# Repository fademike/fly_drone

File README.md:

# fly_drone

My example drone. (in development)

How to connect:
Android phone (AppFlyControl) <-> usb-uart(example: cp2102) <-> uart->rf (STM8S003_AND_SI4463) <-> fly_drone
<br>
or:
<br>
Android phone (QGroundControl or AppFlyControl) <-wifi-> Linux PC (flyLinuxServer) <-> uart->rf (STM8S003_AND_SI4463) <-> fly_drone

on board:
- DC-DC for 2,3,..S battery operation. To operate on a 1S battery, it is necessary to replace the components to turn off the DC-DC.
- RF SI4463 433MHz radio transceiver. when changing the frequency, you can to change components and programmatically set a different frequency.
- imu mpu6050
- 4pcs 3-pin connector for servo motor/ESC (IMP 1-2 ms) for 4pcs brushed motors need to set mosfet or esc for brushed motors.
- i2c connector, for example: for VL53L0X
- connector for debugging by swdio/uart

For connect brushed motors with esc or servo motor, you can use convertor on attiny13a. example: kicad->tiny_2nmosfet.
For connect 4pcs brushed motors, you can use n-mosfet on every channel.

<br>
Code:
<br>
bootloader (update firmware via RF by FlyLinuxServer)<br>
fly_drone<br>
- mavlink protocol:<br>
-- params list settings(PID, mux chan, motor settings, orientation)<br>
-- RC_CHANNELS<br>
-- COMMAND_LONG - ARM_DISARM/CALIBRATION/REBOOT<br>
-- MSG_STATUSTEXT - logs<br>
- imu, rf, vl53l0x<br>
- acc and gyro calibrate<br>
- for save params and acc calibrate on flash, need to change "flash_params"<br>
- it is compatible with qgroungcontrol (tested on android)<br>
<br>
And in repository:<br>
kicad:<br>
- ESC_atmega8 - esc for brashless motor. (need to changed frequency by fuses)<br>
- stm32f103_Fly.. - fly_drone project<br>
- tiny_2nmosfet - esc for connection 4 brashed motors(independent 4 in, 4 out)<br>
<br>
video fly_drone.mpg in video repository

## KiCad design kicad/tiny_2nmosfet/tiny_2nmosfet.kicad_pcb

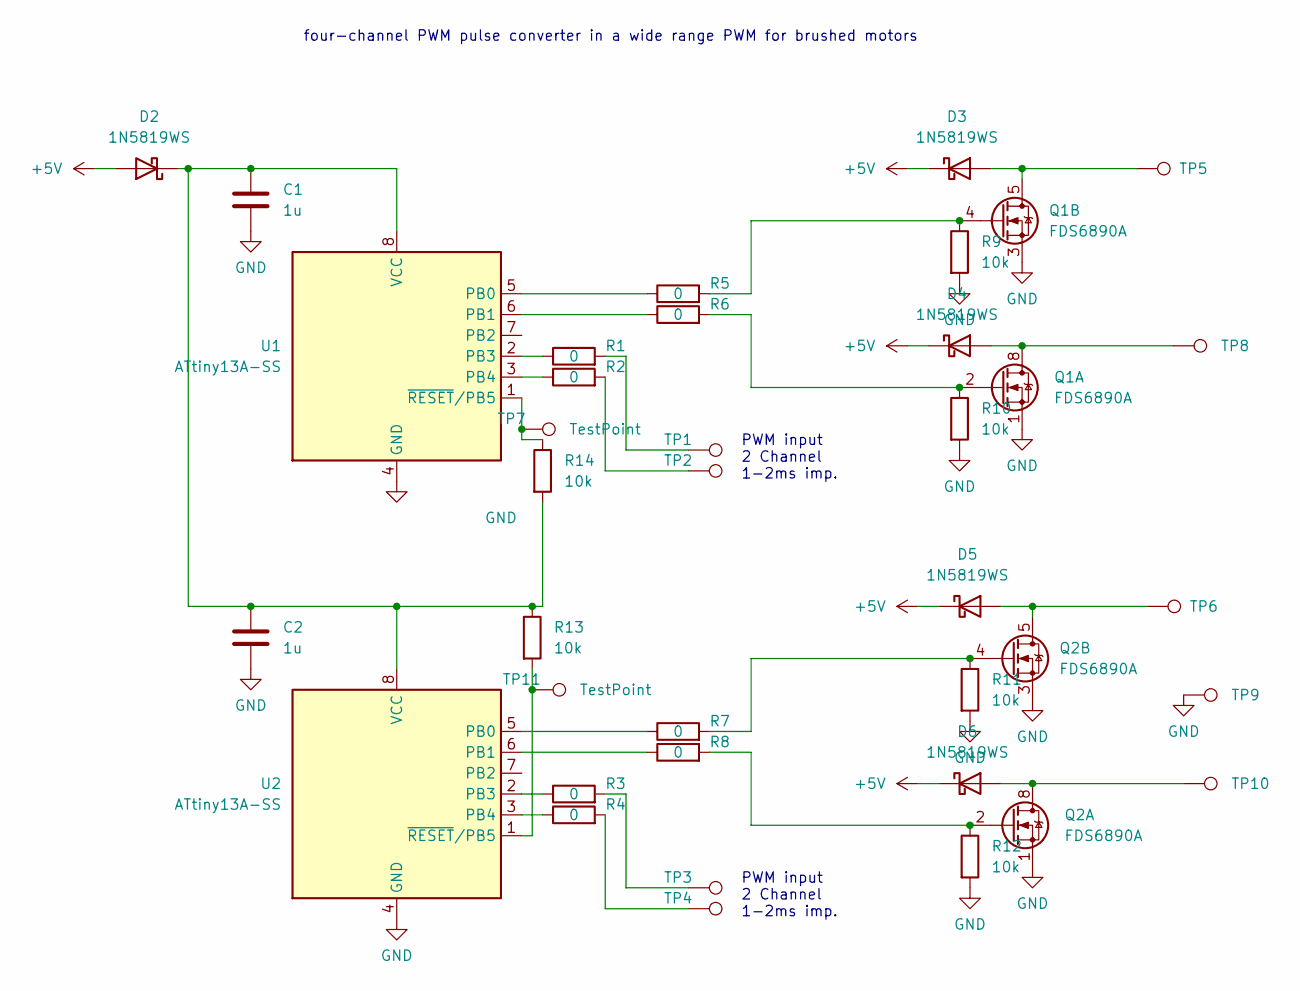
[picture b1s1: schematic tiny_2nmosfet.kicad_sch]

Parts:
C1, C2: 1u; C_0603_1608Metric
D2, D3, D4, D5, D6: 1N5819WS; D_SOD-323
Q1, Q2: FDS6890A; SOIC-8_3.9x4.9mm_P1.27mm
R1, R2, R3, R4, R5, R6, R7, R8: 0; R_0603_1608Metric
R9, R10, R11, R12, R13, R14: 10k; R_0603_1608Metric
TP1, TP2, TP3, TP4, TP5, TP6, TP7, TP8, TP9, TP10, TP11: TestPoint; PinHeader_1x01_P2.54mm_Vertical
U1, U2: ATtiny13A-SS; SOIC-8_3.9x4.9mm_P1.27mm

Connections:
+5V: D2.2 (A), D3.1 (K), D4.1 (K), D5.1 (K), D6.1 (K)
GND: C1.2, C2.2, Q1.1 (S1), Q1.3 (S2), Q2.1 (S1), Q2.3 (S2), R9.2, R10.2, R11.2, R12.2, TP9.1, U1.4 (GND), U2.4 (GND)
unnamed: C1.1, C2.1, D2.1 (K), R13.1, R14.2, U1.8 (VCC), U2.8 (VCC)
unnamed: D3.2 (A), Q1.5 (D2), Q1.6 (D2), TP5.1
unnamed: D4.2 (A), Q1.7 (D1), Q1.8 (D1), TP8.1
unnamed: D5.2 (A), Q2.5 (D2), Q2.6 (D2), TP6.1
unnamed: D6.2 (A), Q2.7 (D1), Q2.8 (D1), TP10.1
unnamed: Q1.2 (G1), R6.2, R10.1
unnamed: Q1.4 (G2), R5.2, R9.1
unnamed: Q2.2 (G1), R8.2, R12.1
unnamed: Q2.4 (G2), R7.2, R11.1
unnamed: R1.2, TP1.1
unnamed: R2.2, TP2.1
unnamed: R3.2, TP3.1
unnamed: R4.2, TP4.1
unnamed: R5.1, U1.5 (PB0)
unnamed: R6.1, U1.6 (PB1)
unnamed: R1.1, U1.2 (PB3)
unnamed: R2.1, U1.3 (PB4)
unnamed: R14.1, TP7.1, U1.1 (~RESET/PB5)
unnamed: R7.1, U2.5 (PB0)
unnamed: R8.1, U2.6 (PB1)
unnamed: R3.1, U2.2 (PB3)
unnamed: R4.1, U2.3 (PB4)
unnamed: R13.2, TP11.1, U2.1 (~RESET/PB5)

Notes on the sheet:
PWM input 2 Channel 1-2ms imp.
four-channel PWM pulse converter in a wide range PWM for brushed motors

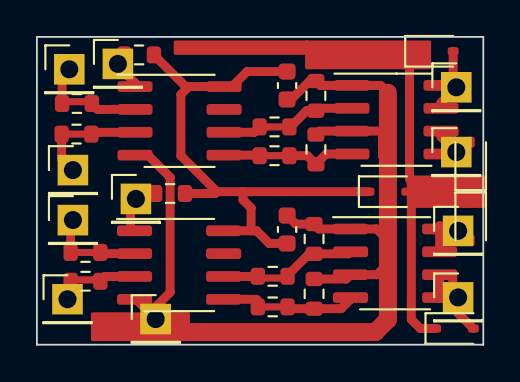
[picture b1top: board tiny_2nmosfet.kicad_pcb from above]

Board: 2 copper layers, 24.8 x 17.1 mm, 36 parts (0 on the bottom side), 25 nets.

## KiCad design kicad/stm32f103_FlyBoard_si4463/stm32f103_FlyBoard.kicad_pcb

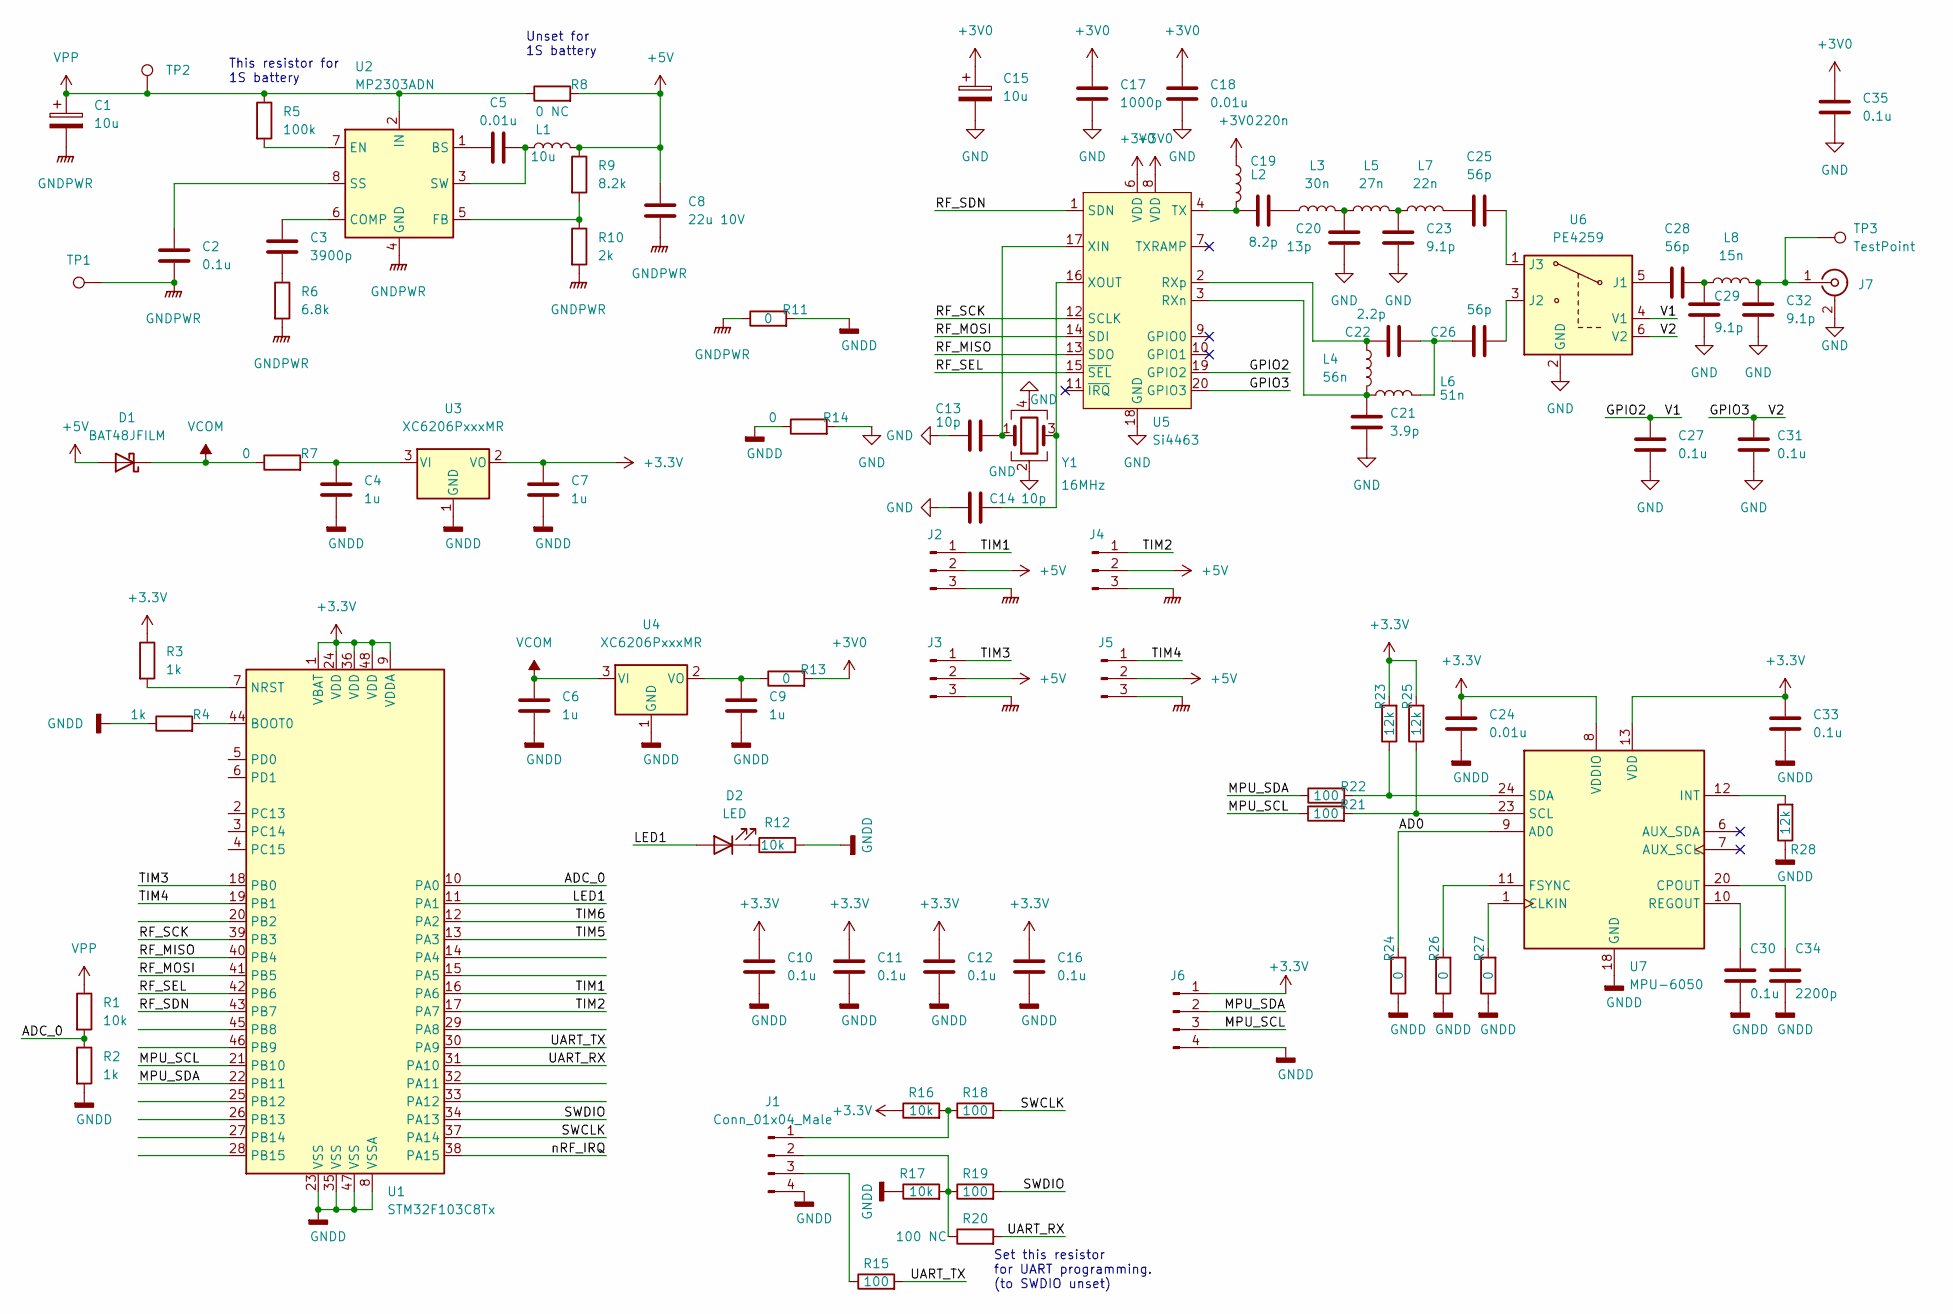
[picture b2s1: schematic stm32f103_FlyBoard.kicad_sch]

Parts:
C1: 10u; CP_EIA-3528-21_Kemet-B
C2, C10, C11, C12, C16, C27, C30, C31, C33, C35: 0.1u; C_0402_1005Metric
C3: 3900p; C_0402_1005Metric
C4, C6, C7, C9: 1u; C_0402_1005Metric
C5, C18, C24: 0.01u; C_0402_1005Metric
C8: 22u 10V; C_0805_2012Metric
C13, C14: 10p; C_0402_1005Metric
C15: 10u; CP_EIA-3216-18_Kemet-A
C17: 1000p; C_0402_1005Metric
C19: 8.2p; C_0402_1005Metric
C20: 13p; C_0402_1005Metric
C21: 3.9p; C_0402_1005Metric
C22: 2.2p; C_0402_1005Metric
C23, C29, C32: 9.1p; C_0402_1005Metric
C25, C26, C28: 56p; C_0402_1005Metric
C34: 2200p; C_0402_1005Metric
D1: BAT48JFILM; D_SOD-323
D2: LED; LED_0805_2012Metric
J1, J6: Conn_01x04_Male; Molex_PicoBlade_53047-0410_1x04_P1.25mm_Vertical
J2, J3, J4, J5: Conn_01x03_Male; Molex_PicoBlade_53047-0310_1x03_P1.25mm_Vertical
J7: Conn_Coaxial; U.FL_Hirose_U.FL-R-SMT-1_Vertical
L1: 10u; L_Bourns-SRN6028
L2: 220n; L_0402_1005Metric
L3: 30n; L_0402_1005Metric
L4: 56n; L_0402_1005Metric
L5: 27n; L_0402_1005Metric
L6: 51n; L_0402_1005Metric
L7: 22n; L_0402_1005Metric
L8: 15n; L_0402_1005Metric
R1, R12, R17: 10k; R_0402_1005Metric
R2, R3, R4: 1k; R_0402_1005Metric
R5: 100k; R_0402_1005Metric
R6: 6.8k; R_0402_1005Metric
R7, R11, R13, R14: 0; R_0805_2012Metric
R8: 0 NC; R_0805_2012Metric
R9: 8.2k; R_0402_1005Metric
R10: 2k; R_0402_1005Metric
R15, R18, R19, R21, R22: 100; R_0402_1005Metric
R16: 10k; R_0603_1608Metric
R20: 100 NC; R_0402_1005Metric
R23, R25, R28: 12k; R_0402_1005Metric
R24, R26, R27: 0; R_0402_1005Metric
TP1, TP2, TP3: TestPoint; TestPoint_Pad_D1.0mm
U1: STM32F103C8Tx; LQFP-48_7x7mm_P0.5mm
U2: MP2303ADN; SOIC-8-1EP_3.9x4.9mm_P1.27mm_EP2.62x3.51mm
U3, U4: XC6206PxxxMR; SOT-23
U5: Si4463; QFN-20-1EP_4x4mm_P0.5mm_EP2.6x2.6mm
U6: PE4259; SOT-363_SC-70-6
U7: MPU-6050; InvenSense_QFN-24_4x4mm_P0.5mm
Y1: 16MHz; Crystal_SMD_SeikoEpson_FA238-4Pin_3.2x2.5mm

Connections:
+3.3V: C7.1, C10.1, C11.1, C12.1, C16.1, C24.1, C33.1, J6.1, R3.1, R16.1, R23.2, R25.2, U1.1 (VBAT), U1.9 (VDDA), U1.24 (VDD), U1.36 (VDD), U1.48 (VDD), U3.2 (VO), U7.8 (VDDIO), U7.13 (VDD)
+3V0: C15.1, C17.1, C18.1, C35.1, L2.1, R13.2, U5.6 (VDD), U5.8 (VDD)
+5V: C8.1, D1.2 (A), J2.2, J3.2, J4.2, J5.2, L1.2, R8.2, R9.1
/AD0: R24.2, U7.9 (AD0)
/ADC_0: R1.2, R2.1, U1.10 (PA0)
/GPIO2: C27.2, U5.19 (GPIO2), U6.4 (V1)
/GPIO3: C31.2, U5.20 (GPIO3), U6.6 (V2)
/LED1: D2.2 (A), U1.11 (PA1)
/MPU_SCL: J6.3, R21.1, U1.21 (PB10)
/MPU_SDA: J6.2, R22.1, U1.22 (PB11)
/RF_MISO: U1.40 (PB4), U5.13 (SDO)
/RF_MOSI: U1.41 (PB5), U5.14 (SDI)
/RF_SCK: U1.39 (PB3), U5.12 (SCLK)
/RF_SDN: U1.43 (PB7), U5.1 (SDN)
/RF_SEL: U1.42 (PB6), U5.15 (~SEL)
/SWCLK: R18.2, U1.37 (PA14)
/SWDIO: R19.2, U1.34 (PA13)
/TIM1: J2.1, U1.16 (PA6)
/TIM2: J4.1, U1.17 (PA7)
/TIM3: J3.1, U1.18 (PB0)
/TIM4: J5.1, U1.19 (PB1)
/TIM5: U1.13 (PA3)
/TIM6: U1.12 (PA2)
/UART_RX: R20.2, U1.31 (PA10)
/UART_TX: R15.2, U1.30 (PA9)
/nRF_IRQ: U1.38 (PA15)
GND: C13.1, C14.1, C15.2, C17.2, C18.2, C20.1, C21.1, C23.1, C27.1, C29.1, C31.1, C32.1, C35.2, J7.2 (Ext), R14.2, U5.18 (GND), U5.21 (GND), U6.2 (GND), Y1.2, Y1.4
GNDD: C4.2, C6.2, C7.2, C9.2, C10.2, C11.2, C12.2, C16.2, C24.2, C30.2, C33.2, C34.2, J1.4, J6.4, R2.2, R4.1, R11.2, R12.2, R14.1, R17.1, R24.1, R26.1, R27.1, R28.1, U1.8 (VSSA), U1.23 (VSS), U1.35 (VSS), U1.47 (VSS), U3.1 (GND), U4.1 (GND), U7.18 (GND)
GNDPWR: C1.2, C2.2, C8.2, J2.3, J3.3, J4.3, J5.3, R6.2, R10.2, R11.1, TP1.1, U2.4 (GND)
unnamed: C3.2, R6.1
unnamed: C19.2, L3.1
unnamed: C20.2, L3.2, L5.1
unnamed: C22.2, C26.1, L6.2
unnamed: C23.2, L5.2, L7.1
unnamed: C25.2, L7.2
unnamed: C28.1, C29.2, L8.1
unnamed: D2.1 (K), R12.1
unnamed: J1.1, R16.2, R18.1
unnamed: J1.2, R17.2, R19.1, R20.1
unnamed: J1.3, R15.1
unnamed: C32.2, J7.1 (In), L8.2, TP3.1
unnamed: R4.2, U1.44 (BOOT0)
unnamed: R3.2, U1.7 (NRST)
unnamed: C5.1, U2.1 (BS)
unnamed: C3.1, U2.6 (COMP)
unnamed: R5.2, U2.7 (EN)
unnamed: R9.2, R10.1, U2.5 (FB)
unnamed: C2.1, U2.8 (SS)
unnamed: C5.2, L1.1, U2.3 (SW)
unnamed: C4.1, R7.2, U3.3 (VI)
unnamed: C9.1, R13.1, U4.2 (VO)
unnamed: C21.2, L4.2, L6.1, U5.3 (RXn)
unnamed: C22.1, L4.1, U5.2 (RXp)
unnamed: C19.1, L2.2, U5.4 (TX)
unnamed: C13.2, U5.17 (XIN), Y1.1
unnamed: C14.2, U5.16 (XOUT), Y1.3
unnamed: C28.2, U6.5 (J1)
unnamed: C26.2, U6.3 (J2)
unnamed: C25.1, U6.1 (J3)
unnamed: R27.2, U7.1 (CLKIN)
unnamed: C34.1, U7.20 (CPOUT)
unnamed: R26.2, U7.11 (FSYNC)
unnamed: R28.2, U7.12 (INT)
unnamed: C30.1, U7.10 (REGOUT)
unnamed: R21.2, R25.1, U7.23 (SCL)
unnamed: R22.2, R23.1, U7.24 (SDA)
VCOM: C6.1, D1.1 (K), R7.1, U4.3 (VI)
VPP: C1.1, R1.1, R5.1, R8.1, TP2.1, U2.2 (IN)

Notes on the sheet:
Unset for 1S battery
Set this resistor for UART programming. (to SWDIO unset)
This resistor for 1S battery

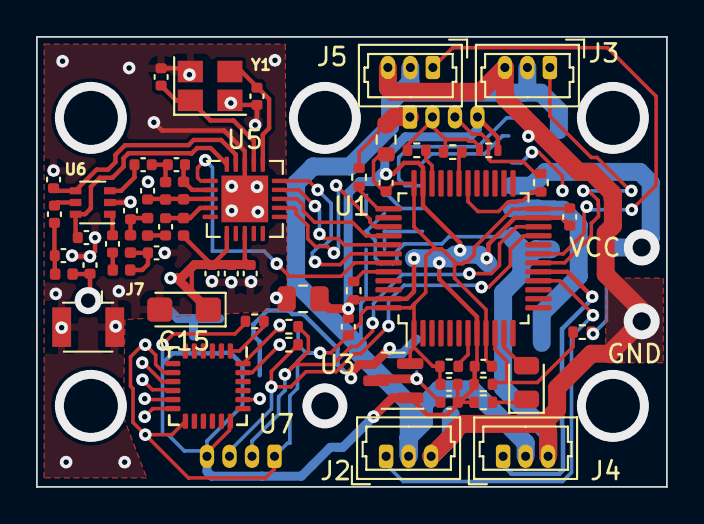
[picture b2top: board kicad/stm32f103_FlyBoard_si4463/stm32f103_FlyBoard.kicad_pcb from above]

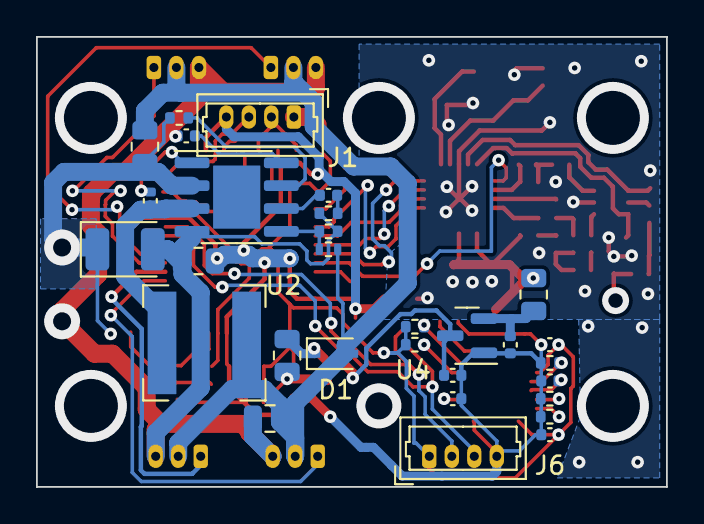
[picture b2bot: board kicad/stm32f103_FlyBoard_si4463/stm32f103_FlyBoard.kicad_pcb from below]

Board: 2 copper layers, 35.0 x 25.0 mm, 91 parts (30 on the bottom side), 65 nets.

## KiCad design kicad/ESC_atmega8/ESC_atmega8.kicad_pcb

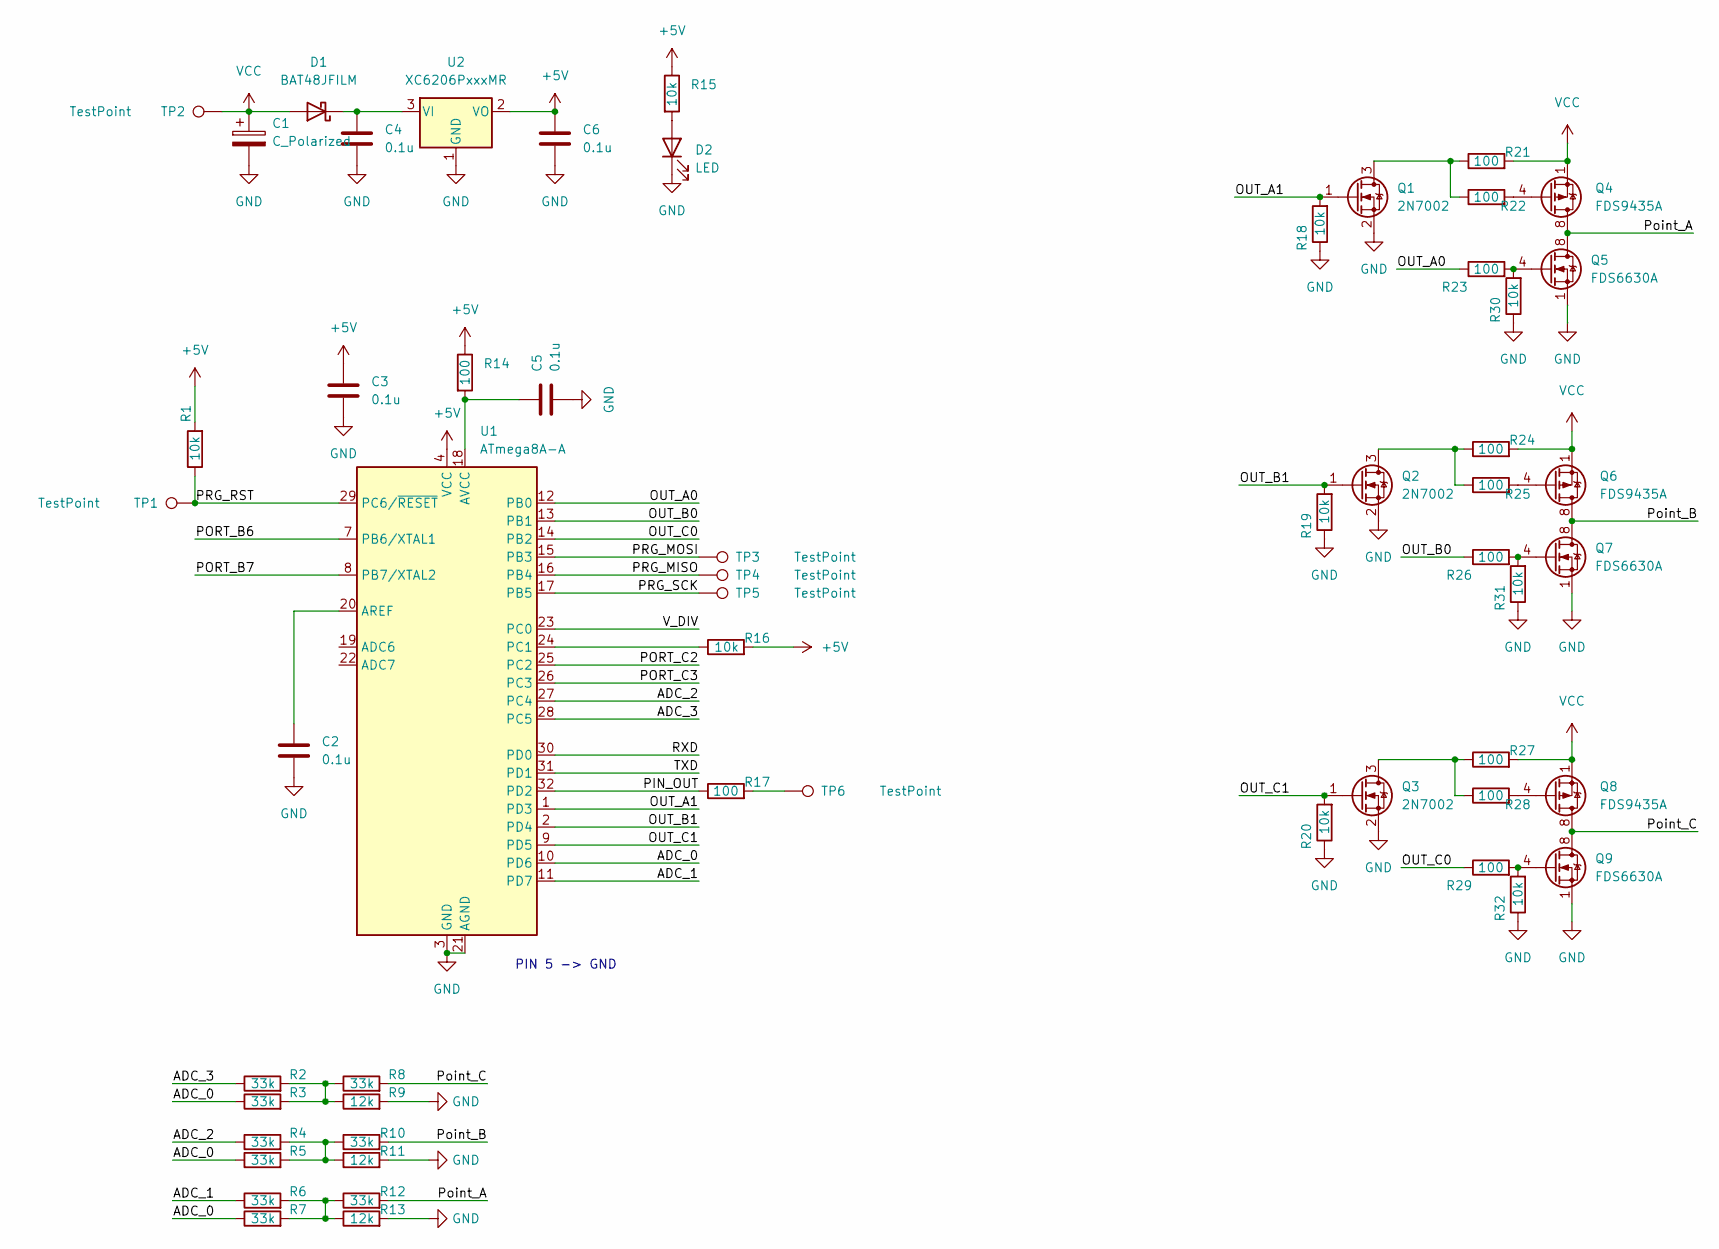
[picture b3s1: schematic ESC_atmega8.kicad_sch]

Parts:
C1: C_Polarized; CP_EIA-6032-28_Kemet-C
C2, C3, C4, C5, C6: 0.1u; C_0603_1608Metric
D1: BAT48JFILM; D_SOD-323
D2: LED; LED_0805_2012Metric
Q1, Q2, Q3: 2N7002; SOT-23
Q4, Q6, Q8: FDS9435A; SOIC-8_3.9x4.9mm_P1.27mm
Q5, Q7, Q9: FDS6630A; SOIC-8_3.9x4.9mm_P1.27mm
R1, R15, R16, R18, R19, R20, R30, R31, R32: 10k; R_0603_1608Metric
R2, R3, R4, R5, R6, R7, R8, R10, R12: 33k; R_0603_1608Metric
R9, R11, R13: 12k; R_0603_1608Metric
R14, R17, R21, R22, R23, R24, R25, R26, R27, R28, R29: 100; R_0603_1608Metric
TP1, TP2, TP3, TP4, TP5, TP6: TestPoint; TestPoint_Pad_D1.0mm
U1: ATmega8A-A; TQFP-32_7x7mm_P0.8mm
U2: XC6206PxxxMR; SOT-23

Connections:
+5V: C3.1, C6.1, R1.2, R14.1, R15.1, R16.2, U1.4 (VCC), U1.6 (VCC), U2.2 (VO)
/ADC_0: R3.1, R5.1, R7.1, U1.10 (PD6)
/ADC_1: R6.1, U1.11 (PD7)
/ADC_2: R4.1, U1.27 (PC4)
/ADC_3: R2.1, U1.28 (PC5)
/OUT_A0: R23.1, U1.12 (PB0)
/OUT_A1: Q1.1 (G), R18.2, U1.1 (PD3)
/OUT_B0: R26.1, U1.13 (PB1)
/OUT_B1: Q2.1 (G), R19.2, U1.2 (PD4)
/OUT_C0: R29.1, U1.14 (PB2)
/OUT_C1: Q3.1 (G), R20.2, U1.9 (PD5)
/PIN_OUT: R17.1, U1.32 (PD2)
/PORT_B6: U1.7 (PB6/XTAL1)
/PORT_B7: U1.8 (PB7/XTAL2)
/PORT_C2: U1.25 (PC2)
/PORT_C3: U1.26 (PC3)
/PRG_MISO: TP4.1, U1.16 (PB4)
/PRG_MOSI: TP3.1, U1.15 (PB3)
/PRG_RST: R1.1, TP1.1, U1.29 (PC6/~RESET)
/PRG_SCK: TP5.1, U1.17 (PB5)
/Point_A: Q4.5 (D), Q4.6 (D), Q4.7 (D), Q4.8 (D), Q5.5 (D), Q5.6 (D), Q5.7 (D), Q5.8 (D), R12.2
/Point_B: Q6.5 (D), Q6.6 (D), Q6.7 (D), Q6.8 (D), Q7.5 (D), Q7.6 (D), Q7.7 (D), Q7.8 (D), R10.2
/Point_C: Q8.5 (D), Q8.6 (D), Q8.7 (D), Q8.8 (D), Q9.5 (D), Q9.6 (D), Q9.7 (D), Q9.8 (D), R8.2
/RXD: U1.30 (PD0)
/TXD: U1.31 (PD1)
/V_DIV: U1.23 (PC0)
GND: C1.2, C2.2, C3.2, C4.2, C5.2, C6.2, D2.1 (K), Q1.2 (S), Q2.2 (S), Q3.2 (S), Q5.1 (S), Q5.2 (S), Q5.3 (S), Q7.1 (S), Q7.2 (S), Q7.3 (S), Q9.1 (S), Q9.2 (S), Q9.3 (S), R9.2, R11.2, R13.2, R18.1, R19.1, R20.1, R30.1, R31.1, R32.1, U1.3 (GND), U1.5 (GND), U1.21 (AGND), U2.1 (GND)
unnamed: C2.1, U1.20 (AREF)
unnamed: C4.1, D1.1 (K), U2.3 (VI)
unnamed: C5.1, R14.2, U1.18 (AVCC)
unnamed: D2.2 (A), R15.2
unnamed: Q1.3 (D), R21.1, R22.1
unnamed: Q2.3 (D), R24.1, R25.1
unnamed: Q3.3 (D), R27.1, R28.1
unnamed: Q4.4 (G), R22.2
unnamed: Q5.4 (G), R23.2, R30.2
unnamed: Q6.4 (G), R25.2
unnamed: Q7.4 (G), R26.2, R31.2
unnamed: Q8.4 (G), R28.2
unnamed: Q9.4 (G), R29.2, R32.2
unnamed: R2.2, R3.2, R8.1, R9.1
unnamed: R4.2, R5.2, R10.1, R11.1
unnamed: R6.2, R7.2, R12.1, R13.1
unnamed: R16.1, U1.24 (PC1)
unnamed: R17.2, TP6.1
VCC: C1.1, D1.2 (A), Q4.1 (S), Q4.2 (S), Q4.3 (S), Q6.1 (S), Q6.2 (S), Q6.3 (S), Q8.1 (S), Q8.2 (S), Q8.3 (S), R21.2, R24.2, R27.2, TP2.1

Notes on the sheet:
PIN 5 -> GND

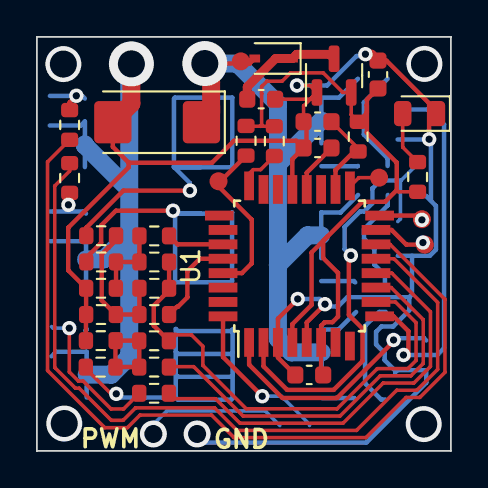
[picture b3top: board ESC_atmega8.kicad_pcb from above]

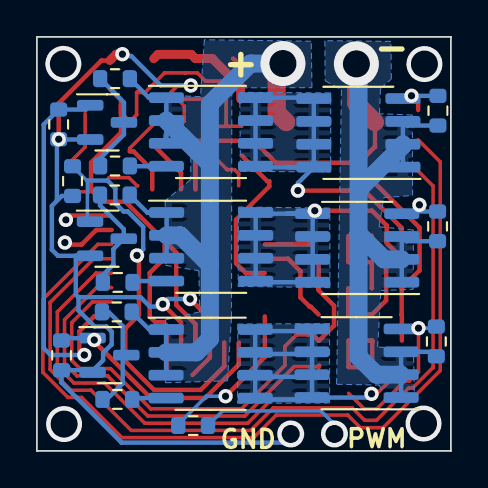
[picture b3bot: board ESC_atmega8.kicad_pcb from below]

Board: 2 copper layers, 23.0 x 23.0 mm, 57 parts (23 on the bottom side), 39 nets.

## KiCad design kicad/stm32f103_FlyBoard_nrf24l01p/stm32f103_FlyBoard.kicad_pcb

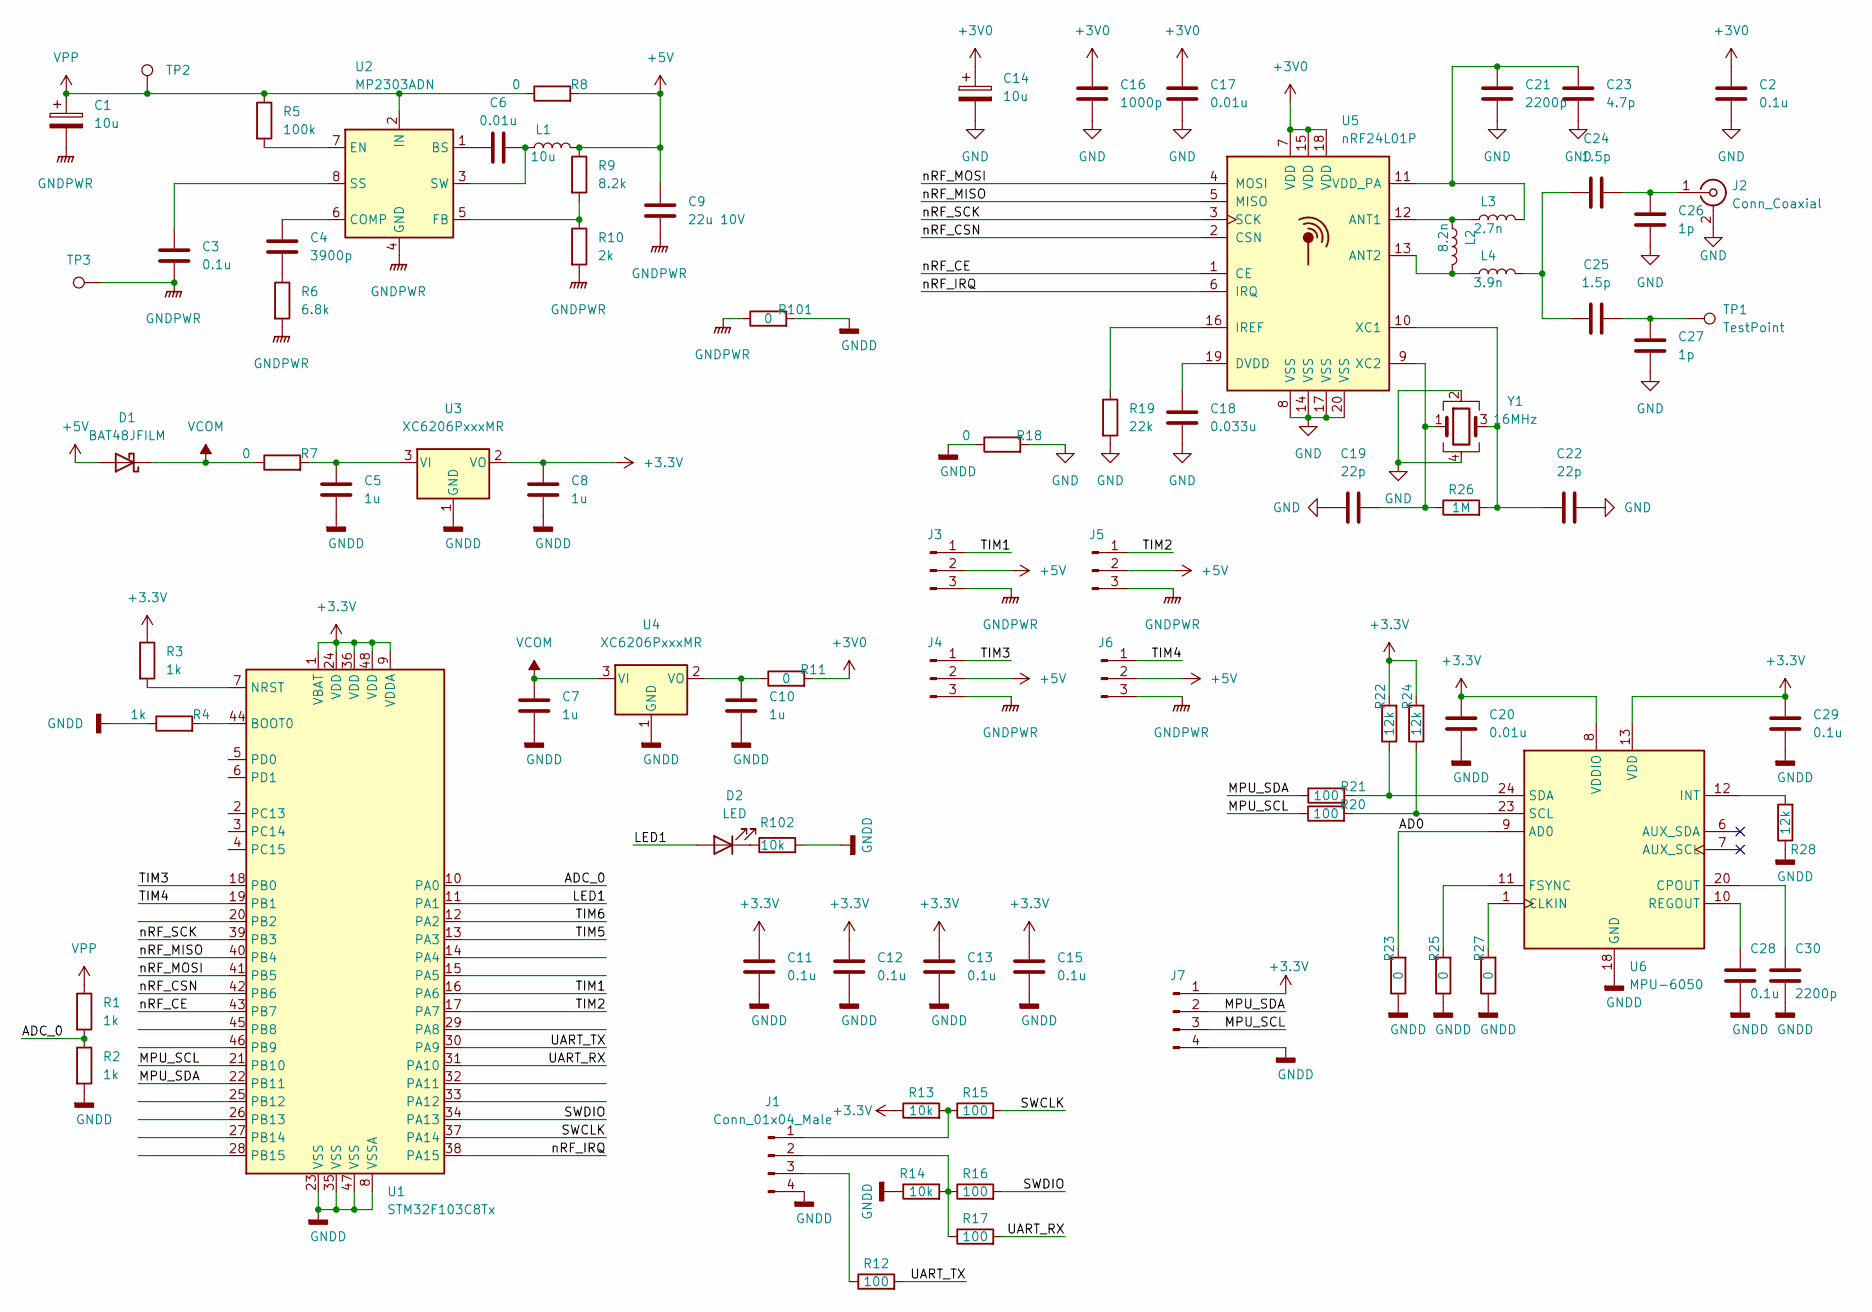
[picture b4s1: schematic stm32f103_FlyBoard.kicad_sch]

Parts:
C1, C14: 10u; CP_EIA-3528-21_Kemet-B
C2, C3, C11, C12, C13, C15, C28, C29: 0.1u; C_0402_1005Metric
C4: 3900p; C_0402_1005Metric
C5, C7, C8, C10: 1u; C_0402_1005Metric
C6, C17, C20: 0.01u; C_0402_1005Metric
C9: 22u 10V; C_0805_2012Metric
C16: 1000p; C_0402_1005Metric
C18: 0.033u; C_0402_1005Metric
C19, C22: 22p; C_0402_1005Metric
C21, C30: 2200p; C_0402_1005Metric
C23: 4.7p; C_0402_1005Metric
C24, C25: 1.5p; C_0402_1005Metric
C26, C27: 1p; C_0402_1005Metric
D1: BAT48JFILM; D_SOD-323
D2: LED; LED_0805_2012Metric
J1, J7: Conn_01x04_Male; Molex_PicoBlade_53047-0410_1x04_P1.25mm_Vertical
J2: Conn_Coaxial; U.FL_Hirose_U.FL-R-SMT-1_Vertical
J3, J4, J5, J6: Conn_01x03_Male; Molex_PicoBlade_53047-0310_1x03_P1.25mm_Vertical
L1: 10u; L_Bourns-SRN6028
L2: 8.2n; L_0402_1005Metric
L3: 2.7n; L_0402_1005Metric
L4: 3.9n; L_0402_1005Metric
R1, R2, R3, R4: 1k; R_0402_1005Metric
R5: 100k; R_0402_1005Metric
R6: 6.8k; R_0402_1005Metric
R7, R8, R11, R18, R101: 0; R_0805_2012Metric
R9: 8.2k; R_0402_1005Metric
R10: 2k; R_0402_1005Metric
R12, R15, R16, R17, R20, R21: 100; R_0402_1005Metric
R13: 10k; R_0603_1608Metric
R14, R102: 10k; R_0402_1005Metric
R19: 22k; R_0402_1005Metric
R22, R24, R28: 12k; R_0402_1005Metric
R23, R25, R27: 0; R_0402_1005Metric
R26: 1M; R_0402_1005Metric
TP1, TP2, TP3: TestPoint; TestPoint_Pad_D1.0mm
U1: STM32F103C8Tx; LQFP-48_7x7mm_P0.5mm
U2: MP2303ADN; SOIC-8-1EP_3.9x4.9mm_P1.27mm_EP2.62x3.51mm
U3, U4: XC6206PxxxMR; SOT-23
U5: nRF24L01P; QFN-20-1EP_4x4mm_P0.5mm_EP2.5x2.5mm
U6: MPU-6050; InvenSense_QFN-24_4x4mm_P0.5mm
Y1: 16MHz; Crystal_SMD_SeikoEpson_FA238-4Pin_3.2x2.5mm

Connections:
+3.3V: C8.1, C11.1, C12.1, C13.1, C15.1, C20.1, C29.1, J7.1, R3.1, R13.1, R22.2, R24.2, U1.1 (VBAT), U1.9 (VDDA), U1.24 (VDD), U1.36 (VDD), U1.48 (VDD), U3.2 (VO), U6.8 (VDDIO), U6.13 (VDD)
+3V0: C2.1, C14.1, C16.1, C17.1, R11.2, U5.7 (VDD), U5.15 (VDD), U5.18 (VDD)
+5V: C9.1, D1.2 (A), J3.2, J4.2, J5.2, J6.2, L1.2, R8.2, R9.1
/AD0: R23.2, U6.9 (AD0)
/ADC_0: R1.2, R2.1, U1.10 (PA0)
/LED1: D2.2 (A), U1.11 (PA1)
/MPU_SCL: J7.3, R20.1, U1.21 (PB10)
/MPU_SDA: J7.2, R21.1, U1.22 (PB11)
/SWCLK: R15.2, U1.37 (PA14)
/SWDIO: R16.2, U1.34 (PA13)
/TIM1: J3.1, U1.16 (PA6)
/TIM2: J5.1, U1.17 (PA7)
/TIM3: J4.1, U1.18 (PB0)
/TIM4: J6.1, U1.19 (PB1)
/TIM5: U1.13 (PA3)
/TIM6: U1.12 (PA2)
/UART_RX: R17.2, U1.31 (PA10)
/UART_TX: R12.2, U1.30 (PA9)
/nRF_CE: U1.43 (PB7), U5.1 (CE)
/nRF_CSN: U1.42 (PB6), U5.2 (CSN)
/nRF_IRQ: U1.38 (PA15), U5.6 (IRQ)
/nRF_MISO: U1.40 (PB4), U5.5 (MISO)
/nRF_MOSI: U1.41 (PB5), U5.4 (MOSI)
/nRF_SCK: U1.39 (PB3), U5.3 (SCK)
GND: C2.2, C14.2, C16.2, C17.2, C18.2, C19.1, C21.2, C22.2, C23.2, C26.2, C27.2, J2.2 (Ext), R18.2, R19.2, U5.8 (VSS), U5.14 (VSS), U5.17 (VSS), U5.20 (VSS), U5.21, Y1.2, Y1.4
GNDD: C5.2, C7.2, C8.2, C10.2, C11.2, C12.2, C13.2, C15.2, C20.2, C28.2, C29.2, C30.2, J1.4, J7.4, R2.2, R4.1, R14.1, R18.1, R23.1, R25.1, R27.1, R28.1, R101.2, R102.2, U1.8 (VSSA), U1.23 (VSS), U1.35 (VSS), U1.47 (VSS), U3.1 (GND), U4.1 (GND), U6.18 (GND)
GNDPWR: C1.2, C3.2, C9.2, J3.3, J4.3, J5.3, J6.3, R6.2, R10.2, R101.1, TP3.1, U2.4 (GND)
unnamed: C3.1, U2.8 (SS)
unnamed: C4.1, U2.6 (COMP)
unnamed: C4.2, R6.1
unnamed: C5.1, R7.2, U3.3 (VI)
unnamed: C6.1, U2.1 (BS)
unnamed: C6.2, L1.1, U2.3 (SW)
unnamed: C10.1, R11.1, U4.2 (VO)
unnamed: C18.1, U5.19 (DVDD)
unnamed: C19.2, R26.1, U5.9 (XC2), Y1.1
unnamed: C21.1, C23.1, L3.2, U5.11 (VDD_PA)
unnamed: C22.1, R26.2, U5.10 (XC1), Y1.3
unnamed: C24.1, C25.1, L4.2
unnamed: C24.2, C26.1, J2.1 (In)
unnamed: C25.2, C27.1, TP1.1
unnamed: C28.1, U6.10 (REGOUT)
unnamed: C30.1, U6.20 (CPOUT)
unnamed: D2.1 (K), R102.1
unnamed: J1.1, R13.2, R15.1
unnamed: J1.2, R14.2, R16.1, R17.1
unnamed: J1.3, R12.1
unnamed: L2.1, L3.1, U5.12 (ANT1)
unnamed: L2.2, L4.1, U5.13 (ANT2)
unnamed: R3.2, U1.7 (NRST)
unnamed: R4.2, U1.44 (BOOT0)
unnamed: R5.2, U2.7 (EN)
unnamed: R9.2, R10.1, U2.5 (FB)
unnamed: R19.1, U5.16 (IREF)
unnamed: R20.2, R24.1, U6.23 (SCL)
unnamed: R21.2, R22.1, U6.24 (SDA)
unnamed: R25.2, U6.11 (FSYNC)
unnamed: R27.2, U6.1 (CLKIN)
unnamed: R28.2, U6.12 (INT)
VCOM: C7.1, D1.1 (K), R7.1, U4.3 (VI)
VPP: C1.1, R1.1, R5.1, R8.1, TP2.1, U2.2 (IN)

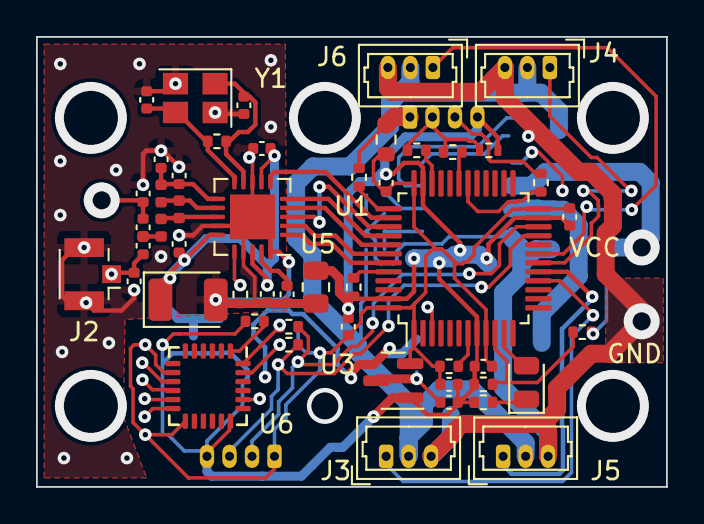
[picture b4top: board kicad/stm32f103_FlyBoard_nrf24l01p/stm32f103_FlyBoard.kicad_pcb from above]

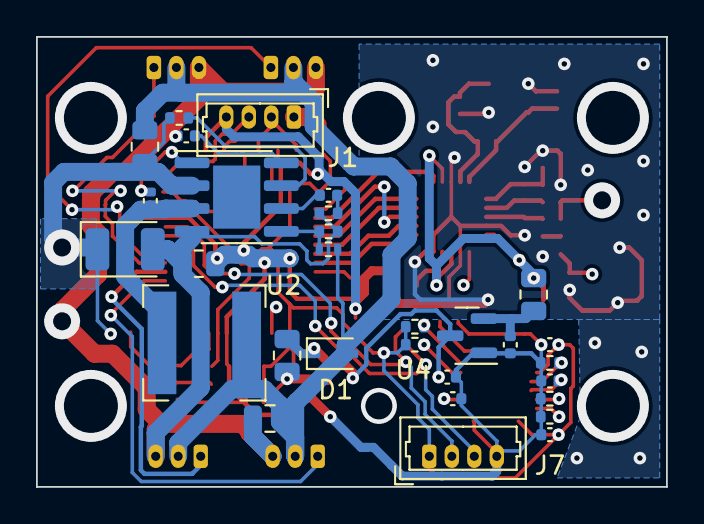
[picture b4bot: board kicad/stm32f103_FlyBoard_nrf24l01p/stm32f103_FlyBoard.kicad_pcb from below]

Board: 2 copper layers, 35.0 x 25.0 mm, 83 parts (30 on the bottom side), 59 nets.

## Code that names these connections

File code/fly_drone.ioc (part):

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Mcu.Name=STM32F103C(8-B)Tx
Mcu.Package=LQFP48
Mcu.UserName=STM32F103C8Tx
PA0-WKUP.Signal=ADCx_IN0
PA1.GPIOParameters=GPIO_Label
PA1.GPIO_Label=PIN_TEST
PA1.Signal=GPIO_Output
PA10.Mode=Asynchronous
PA10.Signal=USART1_RX
PA13.Mode=Serial_Wire
PA13.Signal=SYS_JTMS-SWDIO
PA14.Mode=Serial_Wire
PA14.Signal=SYS_JTCK-SWCLK
PA3.Signal=S_TIM2_CH4
PA6.Signal=S_TIM3_CH1
PA7.Signal=S_TIM3_CH2
PA9.Mode=Asynchronous
PA9.Signal=USART1_TX
PB0.Signal=S_TIM3_CH3
PB1.Signal=S_TIM3_CH4
PB10.Mode=I2C
PB10.Signal=I2C2_SCL
PB11.Mode=I2C
PB11.Signal=I2C2_SDA
PB3.Mode=Full_Duplex_Master
PB3.Signal=SPI1_SCK
PB4.Mode=Full_Duplex_Master
PB4.Signal=SPI1_MISO
PB5.Mode=Full_Duplex_Master
PB5.Signal=SPI1_MOSI
PB6.GPIOParameters=GPIO_Label
PB6.GPIO_Label=SPI1_NSS
PB6.Signal=GPIO_Output
PB7.GPIOParameters=GPIO_Label
PB7.GPIO_Label=SI_SDN
PB7.Signal=GPIO_Output
PC13-TAMPER-RTC.GPIOParameters=GPIO_Label
PC13-TAMPER-RTC.GPIO_Label=PIN_TEST2
PC13-TAMPER-RTC.Signal=GPIO_Output
RCC.SYSCLKFreq_VALUE=64000000
RCC.SYSCLKSource=RCC_SYSCLKSOURCE_PLLCLK
board=custom

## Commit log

2023-03-19 Filled in for a start
2023-05-29 with nRf24 worked. will be write for rf si4463
2023-06-09 worked si4463 for quadcopter
2023-06-15 changed params
2023-08-23 upgraded modem ipu params ...
2024-02-17 added BL, corrected modem control
2024-03-22 added vl53l0x dirty
2024-05-31 after update cubemx
2024-06-08 now it is compatible with qgroungcontrol
2024-06-22 updated params and changed work for car
2024-09-28 changed: altitude hold, parameters, firmware address shifted
2024-10-25 cooperative RTOS scheduler. sysTick
2024-10-25 preemption RTOS scheduler. bootloader and main code in one folder
2024-10-25 bootloader and main code in one folder. firmware address shifted to back
2024-11-23 added chan offset for compatibility with the car.
